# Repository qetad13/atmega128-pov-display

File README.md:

# ATmega128 POV Display — 회전 LED 잔상 디스플레이

> 마이크로프로세서 수업 Term Project · **2025.08 – 2025.11** · 4인 팀 (팀장) — 회로·PCB·펌웨어·기구 설계 전담

## 프로젝트 개요

| | |
|---|---|
| **소개** | 세로 한 줄로 배치한 **RGB LED 16개**를 모터로 회전시키고, 회전에 맞춰 열(column) 데이터를 빠르게 바꿔 **잔상(POV)으로 글자와 그림을 공중에 그리는** 디스플레이. LED 구동 PCB 설계 → 펌웨어 → 3D 프린팅 기구까지 직접 구현했습니다. |
| **기획 의도** | LED 16개는 그 자체로는 세로 **선** 하나에 불과합니다. 하지만 이 선을 회전시키면서 정확한 타이밍에 빛을 바꾸면, 사람 눈의 잔상 효과로 선이 지나간 자리가 **면**이 되어 글자와 그림이 떠오릅니다. **부품 수를 늘리는 대신 시간으로 해상도를 만든다**는 발상에 끌려 주제로 골랐습니다.<br><br>같은 발상을 배선에도 적용했습니다. RGB LED 16개를 직접 제어하려면 핀이 48개 필요하지만, 시프트 레지스터 6개를 한 줄로 엮어 데이터를 직렬로 흘려보내면 **핀 3개면 충분합니다.** 수업에서 배운 ATmega128의 **타이머 · PWM · 외부 인터럽트 · GPIO 제어**를 이 하나의 작품에 통합했고, 이전 프로젝트에서 겪은 만능기판 배선의 한계를 넘기 위해 **KiCad로 PCB를 직접 설계**했습니다. |
| **하이라이트** | 🔆 **선 → 면** : LED 한 줄(16개)을 회전시켜 잔상으로 2차원 화면 구현<br>📌 **48 → 3** : 74HC595 체인으로 LED 48채널을 MCU 핀 3개로 제어<br>🎨 **단색 8행 → RGB 16행** : 해상도 2배, 6색 · 6단계 밝기 표현 |
| **내 역할** | **팀장** — 회로 설계, PCB 아트웍·제작, 펌웨어(LED 보드 · 모터 보드), 기구 3D 모델링, 설계 문서 |
| **기여도** | **90%** — 하드웨어·펌웨어·기구 설계를 사실상 단독으로 구현 (자세한 내용은 [내 담당 범위](#내-담당-범위)) |

## 주요 사양

| 항목 | 내용 |
|---|---|
| MCU | ATmega128 × 2 (LED 보드 / 모터 보드) |
| LED | RGB LED 16개 (16행 × R·G·B = 48채널) |
| LED 드라이버 | 74HC595 ×6 데이지 체인 (48비트) — **MCU 핀 3개로 48채널 구동** |
| 모터 | DC 모터 + L298N 모터 드라이버, Timer0 Fast PWM 속도 제어 |
| 입력 | 택트 스위치 → 외부 인터럽트 (LED 4개 + 모터 3개) |
| 기능 | 6색 전환 · 6단계 밝기 · 패턴 2종(글자 `ISA` / 하트) · 모터 속도 ±, 일시정지 |
| 개발 환경 | CodeVisionAVR (C), KiCad 9, Fusion 360 |
| 상태 | **완료** — 2025.08 – 2025.11 마이크로프로세서 수업 텀프로젝트 (이후 추가 개발 없음) |

<p align="center">

  <br><sub>왼쪽 완성품 · 오른쪽 회전 중 잔상 — LED 한 줄이 회전하며 구(球) 형태의 면을 만듦</sub>
</p>

---

## 시스템 구조

- **고정부**: 12V 어댑터 → L298N이 모터를 구동하고, L298N의 5V 출력으로 모터 보드와 회전부에 전원 공급
- **회전부**: 전원은 **슬립링**을 통해 회전판 위 LED 보드로 전달되며, MCU가 74HC595 체인으로 RGB LED 16개를 구동

### 동작 원리

1. **LED 한 열 출력** — 16비트 열 패턴을 색상에 따라 R/G/B 채널에 배치하고, B → G → R 순서로 48비트를 시프트한 뒤 RCLK로 한 번에 래치
   - 비트가 `0`이면 LED 켜짐(Active-Low), `0xFFFF`는 전체 소등
2. **밝기 (소프트웨어 PWM)** — 한 열을 `uptime` ms 동안 켜고 `7 - uptime` ms 동안 꺼서, 7 ms 주기 안에서 듀티비를 1/7 ~ 6/7로 조절
3. **패턴** — 회전하는 동안 열 데이터를 순서대로 바꿔 출력하면 잔상으로 2차원 이미지가 보임
   - `ISA` 글자: 24열 (글자당 8열), 하트: 12열
4. **모터 속도** — Timer0 Fast PWM의 `OCR0` 값(0~254)을 인터럽트로 ±10씩 바꿔 L298N ENA에 입력

### 제어 흐름

### 핀 배치

**LED 보드 (ATmega128 #1)**

| 핀 | 방향 | 용도 |
|---|---|---|
| PA0 | 출력 | 74HC595 SER / DS (직렬 데이터) |
| PA1 | 출력 | 74HC595 SRCLK / SHCP (시프트 클럭) |
| PA2 | 출력 | 74HC595 RCLK / STCP (래치 클럭) |
| PD0 (INT0) | 입력, 풀업 | 색상 전환 (빨 → 초 → 파 → 노 → 마젠타 → 청록) |
| PD1 (INT1) | 입력, 풀업 | 밝기 변경 (1 ↔ 6 단계 왕복) |
| PD2 (INT2) | 입력, 풀업 | 패턴 1: `ISA` 글자 |
| PD3 (INT3) | 입력, 풀업 | 패턴 2: 하트 |

**모터 보드 (ATmega128 #2)**

| 핀 | 방향 | 용도 |
|---|---|---|
| PB4 (OC0) | 출력 | PWM → L298N ENA |
| PA0 / PA1 | 출력 | L298N IN1 / IN2 (회전 방향 고정) |
| PD0 (INT0) | 입력, 풀업 | 속도 +10 (최대 254) |
| PD1 (INT1) | 입력, 풀업 | 속도 −10 (최소 1) |
| PD2 (INT2) | 입력, 풀업 | 일시정지 / 재시작 (직전 속도 복원, 첫 시작 160) |

인터럽트는 모두 하강 에지 트리거(`EICRA`)입니다.

---

## 폴더 구조

```
atmega128-pov-display/
├─ firmware/                  CodeVisionAVR C 소스
│  ├─ led_board/main.c        74HC595 48비트 시프트 출력, 색상·밝기·패턴 제어
│  └─ motor_board/main.c      Timer0 Fast PWM 모터 속도 제어
├─ hardware/
│  └─ pcb/                    KiCad 9 프로젝트 (LED 보드)
│     ├─ MPMP.kicad_pro / .kicad_sch / .kicad_pcb
│     └─ gerber/              제작용 Gerber + 드릴 파일
├─ mechanical/                3D 프린팅 부품 (STL)
│  ├─ rotor_plate.stl         회전판 (PCB 장착)
│  ├─ rotor_cover_v2.stl      회전판 덮개
│  ├─ support_upper.stl       지지대 (위)
│  ├─ support_lower.stl       지지대 (아래)
│  ├─ base.stl                받침대
│  └─ base_support.stl        받침대 하부 받침
└─ docs/
   ├─ images/                 블록 다이어그램, 플로우차트, PCB · 3D · 결과 사진
   └─ videos/                 동작 영상
```

---

## 하드웨어

### LED 보드 PCB

- **크기**: 90.3 × 87.2 mm, 2층, 두께 1.6 mm (KiCad 9)
- **구성**
  - ATmega128-16A (TQFP-64) + 크리스털, 22 pF 부하 커패시터, 리셋 스위치
  - 74HC595 × 6 (R·G·B 각 2개, 채널당 16비트) + 칩별 0.1 µF 바이패스 커패시터
  - 8연 저항 네트워크(R_Network08) × 2
  - LED 연결 패드 48개 (R/G/B × 16), 10핀 ISP 헤더 (PE0 / PE1 / PB1 / RESET)
  - 고정용 마운팅 홀 4개
- 48채널 LED 배선을 회전체에 싣기 위해 MCU와 시프트 레지스터를 한 장의 보드로 통합

| PCB 레이아웃 | PCB 3D 뷰 | 회전판 조립 (LED 48채널 배선) |
|:---:|:---:|:---:|
|  |  |  |

브레드보드 테스트를 거친 뒤 PCB로 제작했습니다 ([브레드보드 사진](docs/images/breadboard.jpg)).

### 기구부

- 회전판에 PCB와 LED를 고정하고, 모터 축에 연결해 회전
- 지지대(위/아래)와 받침대로 모터와 회전부를 고정
- 회전부 전원은 슬립링을 통해 공급 (회전하는 LED 보드에 VCC · GND 전달)

| 회전판 · 덮개 | 지지대 · 받침대 | 최종 조립 모델 |
|:---:|:---:|:---:|
|  |  |  |

---

## 결과

### RGB 출력

| Red | Green | Blue |
|:---:|:---:|:---:|
|  |  |  |

### 잔상으로 글자 출력 (`ISA`)

| I | S | A |
|:---:|:---:|:---:|
|  |  |  |

### 동작 영상

▶ [`docs/videos/pattern_demo.mp4`](docs/videos/pattern_demo.mp4) — 회전하며 패턴을 출력하는 모습

---

## 내 담당 범위

4인 팀 프로젝트에서 제가 담당한 부분입니다.

| 파트 | 내용 |
|---|---|
| 회로 / PCB | LED 보드 회로도 설계, PCB 아트웍, Gerber 출력 및 제작 |
| 펌웨어 | LED 보드(시프트 레지스터 구동, 색상·밝기·패턴 제어), 모터 보드(PWM 속도 제어) |
| 기구 | 회전판, 덮개, 지지대, 받침대 3D 모델링 및 출력 |
| 설계 문서 | 블록 다이어그램, 제어 플로우차트, 핀 배치 |

---

## 트러블슈팅

### 1. RGB · 16행으로 확장하자 GPIO가 부족해진 문제
- **배경**: 처음에는 단색 LED 8개(8행)로 설계했으나, 두 가지를 바꾸기로 함
  - 한 가지 색으로 고정된 표현이 아쉬워 **RGB LED**로 변경 → 여러 색상 표현
  - 글자와 그림을 더 선명하게 표시하기 위해 **8행 → 16행**으로 해상도 확장
- **문제**: RGB LED 16개를 GPIO로 직접 제어하면 16행 × R·G·B 3색 = **48핀**이 필요 (단색 8행일 때는 8핀) → ATmega128 포트 대부분을 LED에만 써야 해서 버튼 인터럽트 등 다른 기능에 쓸 핀이 부족
- **해결**: 74HC595 시프트 레지스터 6개를 직렬로 연결해 48비트를 직렬로 전송하고 래치로 한 번에 출력
  - MCU 핀 **3개**(SER · SRCLK · RCLK = PA0~2)만으로 LED 48채널 전체 제어
  - 남은 포트는 버튼 인터럽트(INT0~3)와 ISP 프로그래밍에 사용
- **결과**: 단색 8행 → RGB 16행(6색 표현)으로 확장하면서 LED 제어용 GPIO는 48개 → 3개로 줄임

### 2. MCU를 하나로 합치지 못한 문제 (미해결)
- **상황**: 기능만 보면 ATmega128 하나로 LED 표시와 모터 PWM 제어를 모두 처리할 수 있음
- **원인**: LED 보드는 회전판 위에서 돌고 L298N·모터는 고정부에 있음. MCU를 하나로 합치면 전원뿐 아니라 모터 제어선(PWM, 방향 IN1·IN2)이나 버튼 신호도 슬립링을 거쳐야 하는데, 사용한 **슬립링의 선 수가 부족**해 신호선을 추가로 넘길 수 없었음
- **대응**: 모터 제어부(고정)와 디스플레이부(회전)로 나누어 ATmega128을 각각 사용
- **개선 방향**: 선 수가 더 많은 슬립링을 쓰면 MCU 하나로 통합해 부품 수와 배선을 줄일 수 있음
  - 프로젝트가 종료되어 이 구조로 마무리했고, 이후 수정은 진행하지 않음

---

## 실행 방법

### 1. 펌웨어 빌드 및 업로드
1. CodeVisionAVR에서 새 프로젝트 생성 → Chip: **ATmega128**, 클럭은 보드 크리스털에 맞게 설정
2. LED 보드는 `firmware/led_board/main.c`, 모터 보드는 `firmware/motor_board/main.c`를 프로젝트에 추가
3. Build 후 ISP 프로그래머로 각 보드에 업로드
   - `mega128.h`, `delay.h`는 CodeVisionAVR에 포함된 헤더입니다

### 2. 조작
| 보드 | 스위치 | 동작 |
|---|---|---|
| 모터 | INT2 | 모터 시작 / 일시정지 (전원 투입 시 정지 상태) |
| 모터 | INT0 / INT1 | 속도 증가 / 감소 |
| LED | INT2 / INT3 | `ISA` 글자 / 하트 패턴 |
| LED | INT0 | 색상 전환 (6색) |
| LED | INT1 | 밝기 변경 |

LED 보드는 전원 투입 시 R → G → B를 0.3초씩 켜서 LED 상태를 확인한 뒤 대기합니다.

### 3. PCB 제작
- `hardware/pcb/gerber/` 폴더 전체를 압축해 PCB 제작 업체에 업로드
- 설계 수정은 KiCad 9에서 `hardware/pcb/MPMP.kicad_pro` 열기

### 4. 기구 출력
- `mechanical/*.stl`을 슬라이서에서 열어 3D 프린터로 출력

---

## 기술 스택
`C (CodeVisionAVR)` `AVR ATmega128` · `KiCad 9` · `Fusion 360`

## 라이선스 / 출처
- [MIT License](LICENSE)
- 이 저장소의 코드, 회로 및 기구 설계는 모두 직접 작성했으며 외부 코드는 포함하지 않았습니다.
- `mega128.h`, `delay.h`: CodeVisionAVR 컴파일러 기본 헤더 (저장소에 미포함)
- PCB 회로도/풋프린트: KiCad 기본 라이브러리 심볼·풋프린트 사용 (CC-BY-SA 4.0, 설계물에 대한 예외 조항 적용)

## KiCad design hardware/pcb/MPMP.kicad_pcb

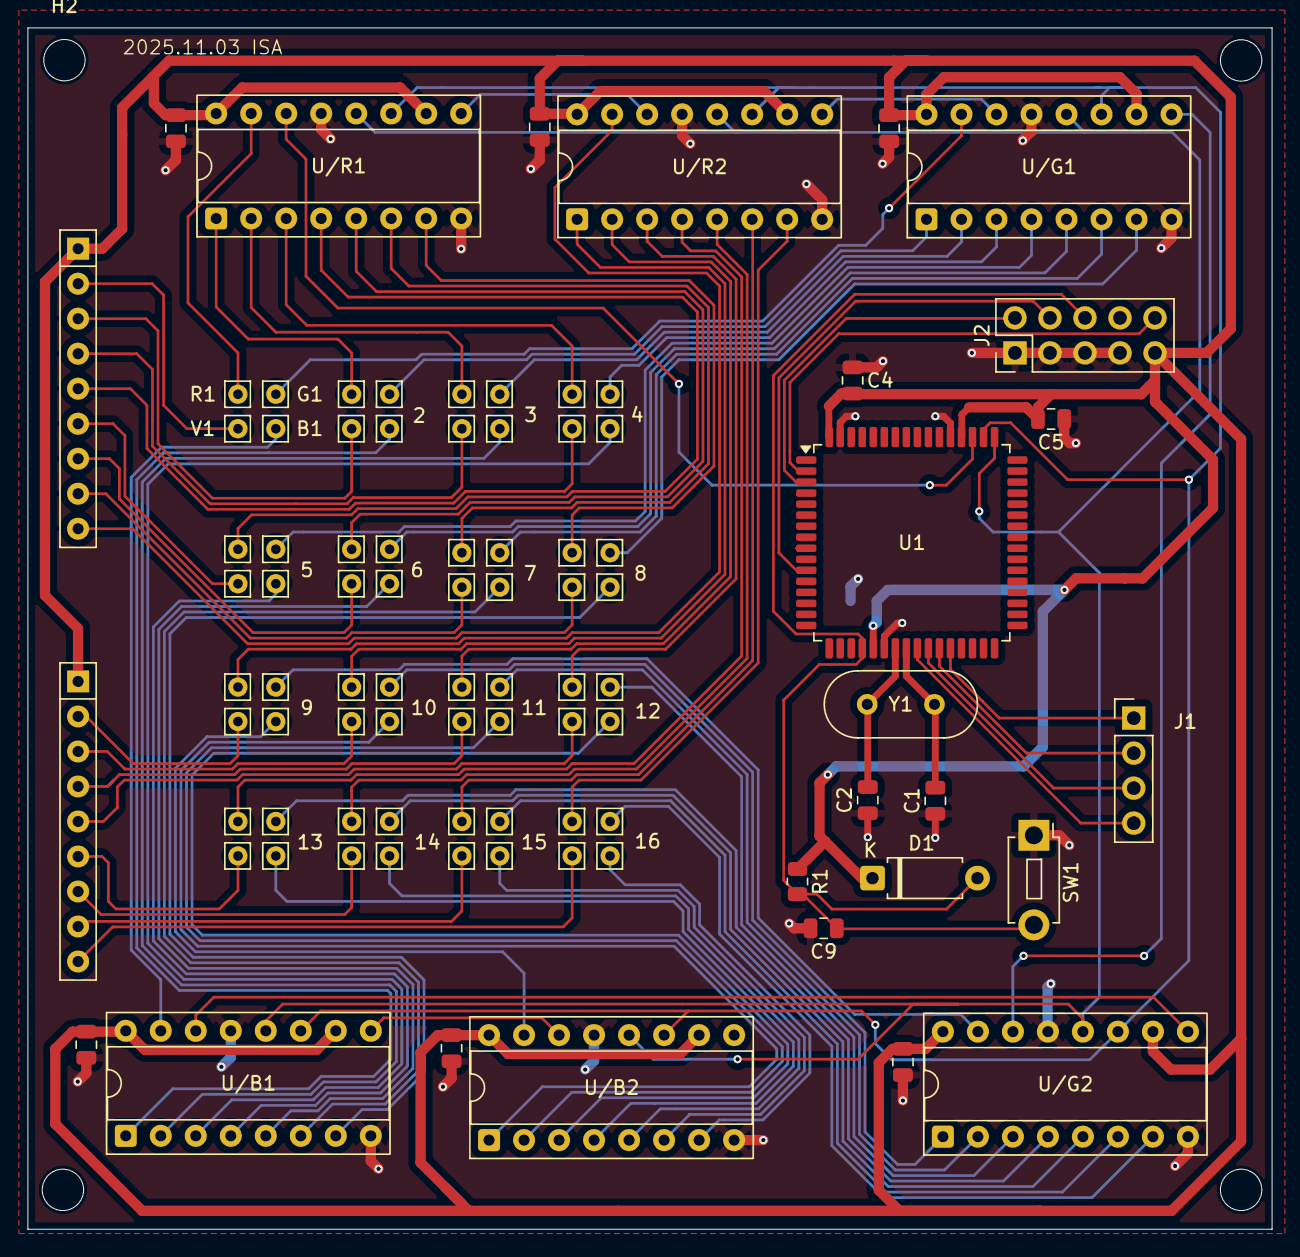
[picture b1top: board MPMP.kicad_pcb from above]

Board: 2 copper layers, 90.3 x 87.2 mm, 95 parts (1 on the bottom side), 84 nets.

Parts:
2, 3, 4, 5, 6, 7, 8, 9, 10, 11, 12, 13, 14, 15, 16: Conn_01x01_Pin; Pin_D0.7mm_L6.5mm_W1.8mm_FlatFork
B1: Conn_01x01_Pin; Pin_D0.7mm_L6.5mm_W1.8mm_FlatFork
C1, C2: 22pF; C_0805_2012Metric
C3, C4, C5: 0.1uF; C_0805_2012Metric
C9: C; C_0805_2012Metric
C/B1, C/B2: C_Small; C_0805_2012Metric
C/G1, C/G2: C_Small; C_0805_2012Metric
C/R1, C/R2: C_Small; C_0805_2012Metric
D1: D; D_A-405_P7.62mm_Horizontal
G1: Conn_01x01_Pin; Pin_D0.7mm_L6.5mm_W1.8mm_FlatFork
H1, H2, H3, H4: MountingHole; MountingHole_3mm
J1: Conn_01x04_Pin; PinHeader_1x04_P2.54mm_Vertical
J2: Conn_01x10_Pin; PinHeader_2x05_P2.54mm_Vertical
J/B2, J/B3, J/B4, J/B5, J/B6, J/B7, J/B8, J/B9, J/B11, J/B12, J/B13, J/B15, J/B16: Conn_01x01_Pin; Pin_D0.7mm_L6.5mm_W1.8mm_FlatFork
J/G10, J/G11, J/G12, J/G14, J/G15, J/G16: Conn_01x01_Pin; Pin_D0.7mm_L6.5mm_W1.8mm_FlatFork
J/R2, J/R3, J/R4, J/R5, J/R6, J/R7, J/R8, J/R9, J/R10, J/R12, J/R13, J/R14, J/R15, J/R16: Conn_01x01_Pin; Pin_D0.7mm_L6.5mm_W1.8mm_FlatFork
J/V2, J/V3, J/V4, J/V5, J/V6, J/V7, J/V8, J/V9, J/V10, J/V11, J/V13, J/V14: Conn_01x01_Pin; Pin_D0.7mm_L6.5mm_W1.8mm_FlatFork
R1: Conn_01x01_Pin; Pin_D0.7mm_L6.5mm_W1.8mm_FlatFork
R1#2: R; R_0805_2012Metric
RN1, RN2: R_Network08; R_Array_SIP9
SW1: SW_SPST; SW_PUSH_1P1T_6x3.5mm_H4.3_APEM_MJTP1243
U1: ATmega128-16A; TQFP-64_14x14mm_P0.8mm
U/B1, U/B2: 74HC595; DIP-16_W7.62mm_Socket
U/G1, U/G2: 74HC595; DIP-16_W7.62mm_Socket
U/R1, U/R2: 74HC595; DIP-16_W7.62mm_Socket
V1: Conn_01x01_Pin; Pin_D0.7mm_L6.5mm_W1.8mm_FlatFork
Y1: Crystal; Crystal_HC49-U_Vertical

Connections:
/PB1: J2.4, U1.11 (PB1)
/PE0: J2.10, U1.2 (PE0)
/PE1: J2.2, U1.3 (PE1)
/RCLK/STCP: U1.49 (PA2), U/B1.12 (RCLK), U/B2.12 (RCLK), U/G1.12 (RCLK), U/G2.12 (RCLK), U/R1.12 (RCLK), U/R2.12 (RCLK)
/RESET: C9.1, D1.2 (A), J2.6, R1#2.2, SW1.2 (B), U1.20 (~RESET)
/SER/DS: U1.51 (PA0), U/R1.14 (SER)
/SRCLK/SHCP: U1.50 (PA1), U/B1.11 (SRCLK), U/B2.11 (SRCLK), U/G1.11 (SRCLK), U/G2.11 (SRCLK), U/R1.11 (SRCLK), U/R2.11 (SRCLK)
GND: C1.1, C2.1, C3.1, C4.1, C5.1, C9.2, C/B1.2, C/B2.2, C/G1.2, C/G2.2, C/R1.2, C/R2.2, J2.1, J2.3, J2.5, J2.7, SW1.1 (A), U1.22 (GND), U1.53 (GND), U1.63 (GND), U/B1.8 (GND), U/B1.13 (~OE), U/B2.8 (GND), U/B2.13 (~OE), U/G1.8 (GND), U/G1.13 (~OE), U/G2.8 (GND), U/G2.13 (~OE), U/R1.8 (GND), U/R1.13 (~OE), U/R2.8 (GND), U/R2.13 (~OE)
unnamed: J1.1, U1.28 (PD3)
unnamed: J1.2, U1.27 (PD2)
unnamed: J1.3, U1.26 (PD1)
unnamed: J1.4, U1.25 (PD0)
unnamed: B1.1, U/B1.15 (QA)
unnamed: J/B2.1, U/B1.1 (QB)
unnamed: J/B3.1, U/B1.2 (QC)
unnamed: J/B4.1, U/B1.3 (QD)
unnamed: J/B5.1, U/B1.4 (QE)
unnamed: J/B6.1, U/B1.5 (QF)
unnamed: J/B7.1, U/B1.6 (QG)
unnamed: J/B8.1, U/B1.7 (QH)
unnamed: J/B9.1, U/B2.15 (QA)
unnamed: 10.1, U/B2.1 (QB)
unnamed: J/B11.1, U/B2.2 (QC)
unnamed: J/B12.1, U/B2.3 (QD)
unnamed: J/B13.1, U/B2.4 (QE)
unnamed: 14.1, U/B2.5 (QF)
unnamed: J/B15.1, U/B2.6 (QG)
unnamed: J/B16.1, U/B2.7 (QH)
unnamed: G1.1, U/G1.15 (QA)
unnamed: 2.1, U/G1.1 (QB)
unnamed: 3.1, U/G1.2 (QC)
unnamed: 4.1, U/G1.3 (QD)
unnamed: 5.1, U/G1.4 (QE)
unnamed: 6.1, U/G1.5 (QF)
unnamed: 7.1, U/G1.6 (QG)
unnamed: 8.1, U/G1.7 (QH)
unnamed: 9.1, U/G2.15 (QA)
unnamed: J/G10.1, U/G2.1 (QB)
unnamed: J/G11.1, U/G2.2 (QC)
unnamed: J/G12.1, U/G2.3 (QD)
unnamed: 13.1, U/G2.4 (QE)
unnamed: J/G14.1, U/G2.5 (QF)
unnamed: J/G15.1, U/G2.6 (QG)
unnamed: J/G16.1, U/G2.7 (QH)
unnamed: R1.1, U/R1.15 (QA)
unnamed: J/R2.1, U/R1.1 (QB)
unnamed: J/R3.1, U/R1.2 (QC)
unnamed: J/R4.1, U/R1.3 (QD)
unnamed: J/R5.1, U/R1.4 (QE)
unnamed: J/R6.1, U/R1.5 (QF)
unnamed: J/R7.1, U/R1.6 (QG)
unnamed: J/R8.1, U/R1.7 (QH)
unnamed: J/R9.1, U/R2.15 (QA)
unnamed: J/R10.1, U/R2.1 (QB)
unnamed: 11.1, U/R2.2 (QC)
unnamed: J/R12.1, U/R2.3 (QD)
unnamed: J/R13.1, U/R2.4 (QE)
unnamed: J/R14.1, U/R2.5 (QF)
unnamed: J/R15.1, U/R2.6 (QG)
unnamed: J/R16.1, U/R2.7 (QH)
unnamed: RN1.2 (R1), V1.1
unnamed: J/V2.1, RN1.3 (R2)
unnamed: J/V3.1, RN1.4 (R3)
unnamed: J/V4.1, RN1.5 (R4)
unnamed: J/V5.1, RN1.6 (R5)
unnamed: J/V6.1, RN1.7 (R6)
unnamed: J/V7.1, RN1.8 (R7)
unnamed: J/V8.1, RN1.9 (R8)
unnamed: J/V9.1, RN2.2 (R1)
unnamed: J/V10.1, RN2.3 (R2)
unnamed: J/V11.1, RN2.4 (R3)
unnamed: 12.1, RN2.5 (R4)
unnamed: J/V13.1, RN2.6 (R5)
unnamed: J/V14.1, RN2.7 (R6)
unnamed: 15.1, RN2.8 (R7)
unnamed: 16.1, RN2.9 (R8)
unnamed: C1.2, U1.24 (XTAL1), Y1.2
unnamed: C2.2, U1.23 (XTAL2), Y1.1
unnamed: U/B1.9 (QH'), U/B2.14 (SER)
unnamed: U/B1.14 (SER), U/G2.9 (QH')
unnamed: U/G1.9 (QH'), U/G2.14 (SER)
unnamed: U/G1.14 (SER), U/R2.9 (QH')
unnamed: U/R1.9 (QH'), U/R2.14 (SER)
VCC: C3.2, C4.2, C5.2, C/B1.1, C/B2.1, C/G1.1, C/G2.1, C/R1.1, C/R2.1, D1.1 (K), J2.9, R1#2.1, RN1.1 (common), RN2.1 (common), U1.21 (VCC), U1.52 (VCC), U1.64 (AVCC), U/B1.10 (~SRCLR), U/B1.16 (VCC), U/B2.10 (~SRCLR), U/B2.16 (VCC), U/G1.10 (~SRCLR), U/G1.16 (VCC), U/G2.10 (~SRCLR), U/G2.16 (VCC), U/R1.10 (~SRCLR), U/R1.16 (VCC), U/R2.10 (~SRCLR), U/R2.16 (VCC)
